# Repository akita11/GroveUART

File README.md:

# GroveUART

GroveケーブルのUART信号を、FTDI-Basic等のUSBシリアル変換器の標準的な6ピンコネクタに接続します。両者の送信(TX)と受信(RX)の接続を切り替えらるので、ストレート結線・リバース結線の両者の使い方ができます。またソルダージャンパをショートすることでFTDI-Basic側の電源をGroveコネクタ側に供給することができます。

## 使い方

M5Stack等からのUART信号の出ているGroveケーブルをGroveコネクタ側に接続し、6ピンコネクタ側には[FTDI-Basic等のUSB-シリアル変換器](https://www.switch-science.com/products/2782)を接続します。Groveケーブル側のUART信号にあわせて、以下のように2箇所のショートピンを設定します。

また裏面のJP1をハンダでショートすることで、FTDI-Basicからの電源をGroveコネクタ側に供給することができます。

### Grove側がUART親機側(M5Stack等)の場合

このようにR-R側、T-T側にショートピンを接続します。これにより、以下のように接続されます。

- Groveの1番ピン（端）: FTDI-BasicのTXD(TXo)側
- Groveの2番ピン（その横）: FTDI-basicのRXD(RXi)側

※Groveの1番／2番ピンは、M5StackのPortCのGPIO16(RXD2)/17(TXD2)(Basicの場合)や、GPIO13(RXD2)/14(TXD2)(Core2)です。

### Grove側がUART子機側(Groveセンサ等等)の場合

このようにR-T側、R-T側にショートピンを接続します。これにより、以下のように接続されます。

- Groveの1番ピン（端）: FTDI-basicのRXD(RXi)側
- Groveの2番ピン（その横）: FTDI-BasicのTXD(TXo)側

※例えばM5Stack UnitV2では、Groveの1番ピンは"Rx”と表記されていますが、これは「接続先(M5StackBasic等)がRx」という意味ですので、UnitV2にとっては出力(TX)です。

## Author

Junichi Akita (akita@ifdl.jp, @akita11)

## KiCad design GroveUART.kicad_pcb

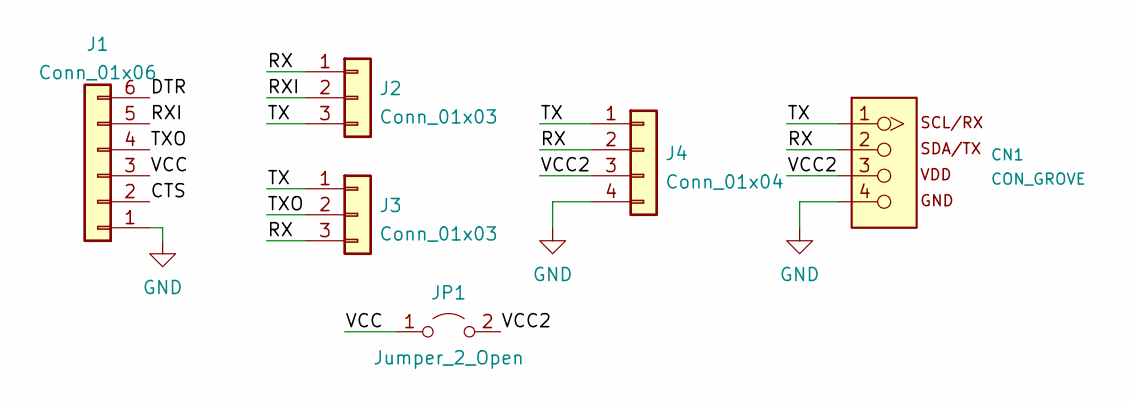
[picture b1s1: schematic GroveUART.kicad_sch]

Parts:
CN1: CON_GROVE; CON_GROVE_H
J1: Conn_01x06; PinHeader_1x06_P2.54mm_Horizontal
J2, J3: Conn_01x03; PinSocket_1x03_P2.54mm_Vertical
J4: Conn_01x04; PinSocket_1x04_P2.54mm_Vertical
JP1: Jumper_2_Open; SolderJumper-2_P1.3mm_Open_Pad1.0x1.5mm

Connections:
/CTS: J1.2
/DTR: J1.6
/RX: CN1.2, J2.1, J3.3, J4.2
/RXI: J1.5, J2.2
/TX: CN1.1, J2.3, J3.1, J4.1
/TXO: J1.4, J3.2
/VCC: J1.3, JP1.1 (A)
/VCC2: CN1.3, J4.3, JP1.2 (B)
GND: CN1.4, J1.1, J4.4

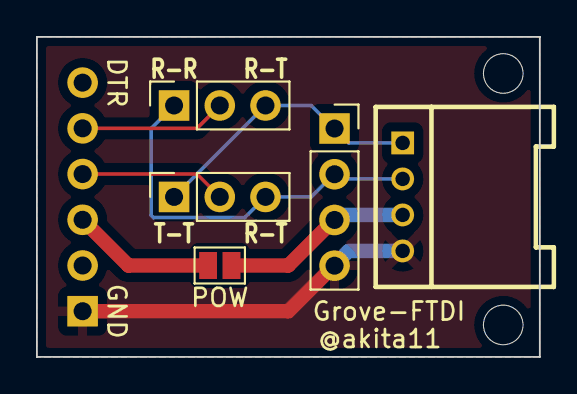
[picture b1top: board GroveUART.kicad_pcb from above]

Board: 2 copper layers, 27.9 x 17.8 mm, 6 parts (0 on the bottom side), 7 nets.
